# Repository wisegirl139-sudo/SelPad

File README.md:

# SelPad
SelPad is a macropad project for hack club.(my first kinda). Its used to select text and work alongside a normal keyboard ,and its functions. My main purpose for creating this is that my current keyboard is rather laggy and the mousepad is even worse.Therefore this project adds to my learning while also being useful in everyday life.
(the file selpad is all the qmk information and stuff, i cant change the name for some reason)

overall

schmatic

pcb

case

BOM:
1X Seeed XIAO RP2040
5x through-hole 1N4148 Diodes
5x MX-Style switches
1x 0.91 inch OLED display 
5x white blank DSA keycaps
5x SK6812 MINI-E LEDs
4x M3x16mm screws
4x M3x5mx4mm heatset inserts

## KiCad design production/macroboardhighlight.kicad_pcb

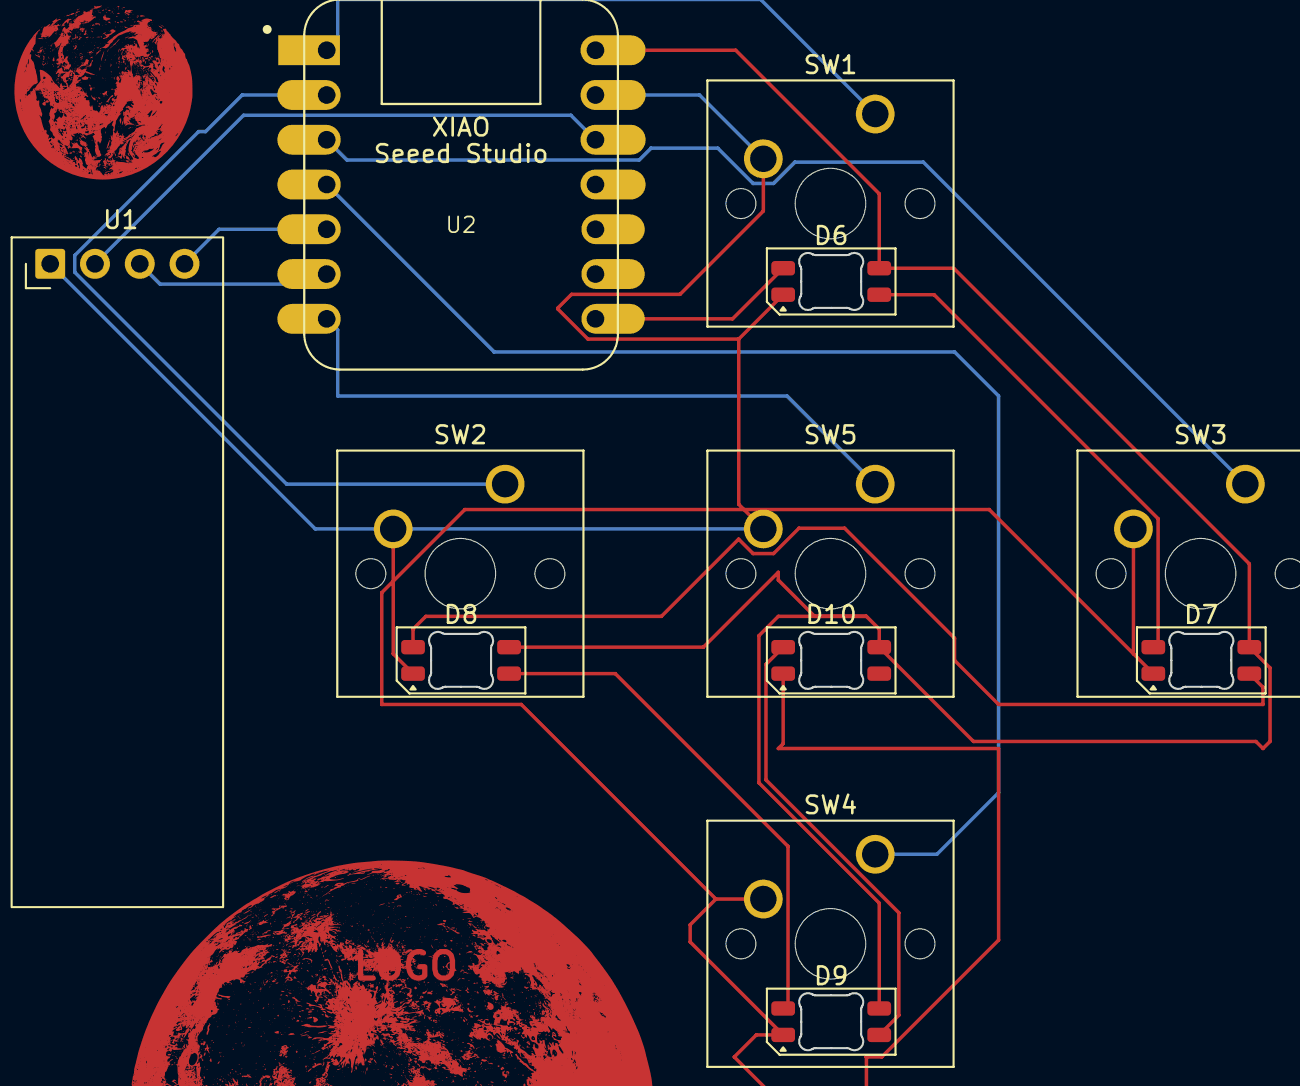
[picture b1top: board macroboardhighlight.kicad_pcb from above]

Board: 2 copper layers, 12 parts (0 on the bottom side), 15 nets.

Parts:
D6, D7, D8, D9, D10: SK6812MINI-E; LED_SK6812MINI-E_3.2x2.8mm_P1.5mm_ReverseMount
SW1, SW2, SW3, SW4, SW5: SW_Push; SW_Cherry_MX_1.00u_PCB
U1: ER_OLEDM0.91_1x-I2C
U2: MOUDLE-SEEEDUINO-XIAO; XIAO-Generic-Hybrid-14P-2.54-21X17.8MM

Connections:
GND: D6.1 (VSS), D7.1 (VSS), D8.1 (VSS), D9.1 (VSS), D10.1 (VSS), SW1.2, SW2.2, SW3.2, SW4.2, SW5.2, U1.1 (GND), U2.13 (GND)
unnamed: D6.2 (DIN), U2.8 (PB09_A7_D7_RX)
unnamed: D6.4 (DOUT), D7.2 (DIN)
unnamed: D7.4 (DOUT), D8.2 (DIN)
unnamed: D8.4 (DOUT), D9.2 (DIN)
unnamed: D9.4 (DOUT), D10.2 (DIN)
unnamed: D6.3 (VDD), D7.3 (VDD), D8.3 (VDD), D9.3 (VDD), D10.3 (VDD), U2.14 (5V)
unnamed: U1.3 (SCL), U2.6 (PA9_A5_D5_SCL)
unnamed: U1.4 (SDA), U2.5 (PA8_A4_D4_SDA)
unnamed: U1.2 (VCC), U2.12 (3V3)
unnamed: SW1.1, U2.1 (PA02_A0_D0)
unnamed: SW2.1, U2.2 (PA4_A1_D1)
unnamed: SW3.1, U2.3 (PA10_A2_D2)
unnamed: SW4.1, U2.4 (PA11_A3_D3)
unnamed: SW5.1, U2.7 (PB08_A6_D6_TX)
